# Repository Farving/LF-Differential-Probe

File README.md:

# Scope-Preamp-x1000
Differential input Scope preamp x1000 for measuring ground plane noise

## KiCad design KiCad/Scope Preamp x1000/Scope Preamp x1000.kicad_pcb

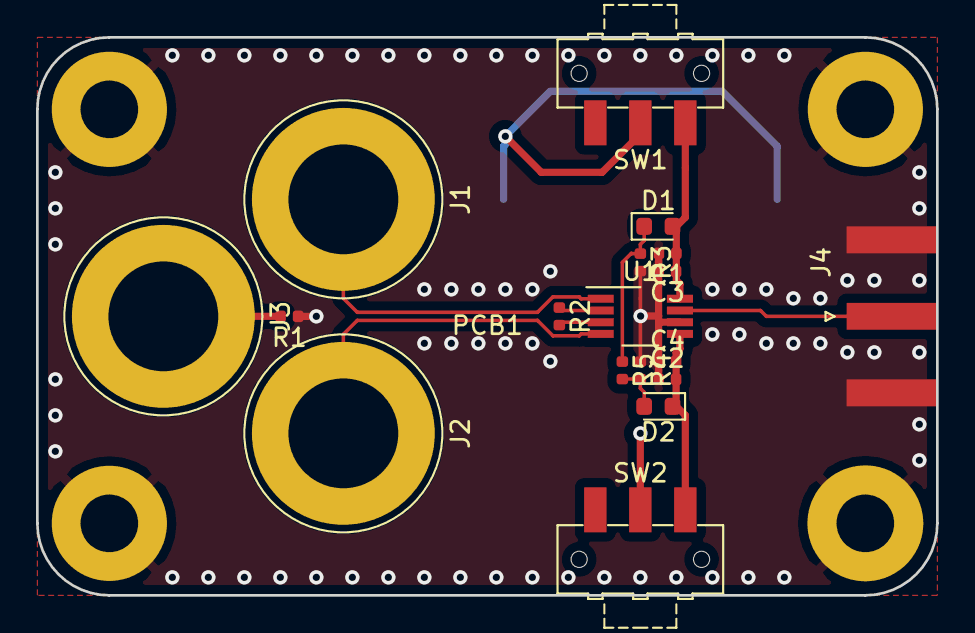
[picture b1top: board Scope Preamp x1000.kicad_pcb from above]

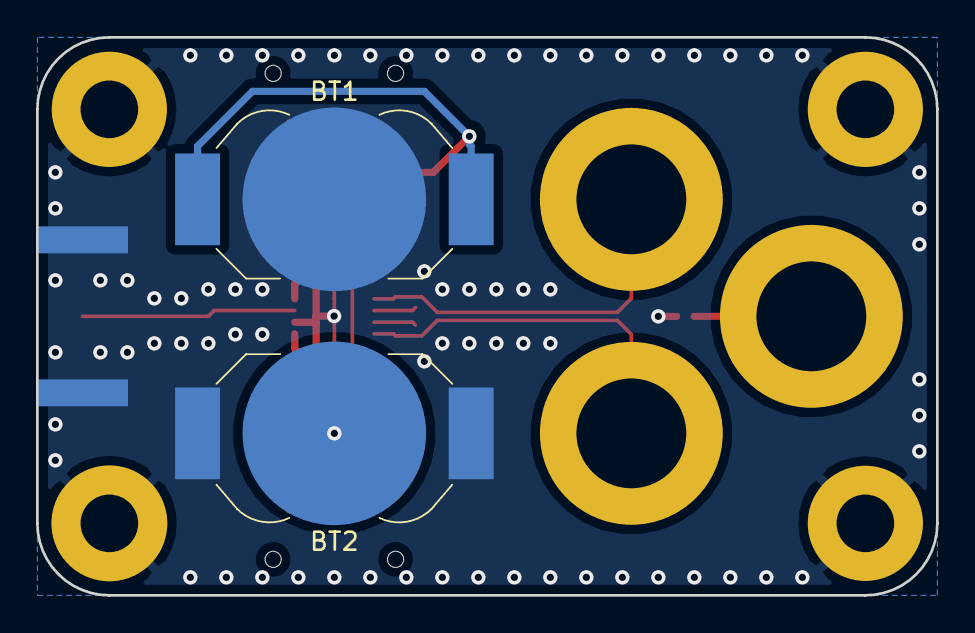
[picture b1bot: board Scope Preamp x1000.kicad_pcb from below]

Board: 2 copper layers, 50.0 x 31.0 mm, 21 parts (2 on the bottom side), 13 nets.

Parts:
BT1, BT2: CR2032; BatteryHolder_LINX_BAT-HLD-012-SMT
C1, C2: 10u; C_0402_1005Metric
C3, C4: 100n; C_0402_1005Metric
D1, D2: LED; LED_0603_1608Metric
J1, J2, J3: Conn_01x01_Male; Banana_Jack_1Pin
J4: Conn_Coaxial; SMA_Amphenol_132289_EdgeMount
PCB1: Board_Module; PCB_Board_50x31
R1: 10R; R_0402_1005Metric
R2, R3, R4, R5: 100R; R_0402_1005Metric
SW1, SW2: SW_SPDT; SW_SPDT_CK-JS102011SAQN
U1: INA826; VSSOP-8_3.0x3.0mm_P0.65mm

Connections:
/IN+: J2.1, U1.4
/IN-: J1.1, U1.1
GND: BT1.2, BT2.1, C1.2, C2.1, C3.2, C4.1, J4.2, PCB1.1, PCB1.2, PCB1.3, PCB1.4, R1.1, R3.2, R4.1, U1.6
unnamed: BT1.1, SW1.2
unnamed: BT2.2, SW2.2
unnamed: D1.1, R3.1, R5.1
unnamed: D2.2, R4.2, R5.2
unnamed: J3.1, R1.2
unnamed: J4.1, U1.7
unnamed: R2.1, U1.2
unnamed: R2.2, U1.3
VDD: C1.1, C3.1, D1.2, SW1.1, U1.8
VEE: C2.2, C4.2, D2.1, SW2.3, U1.5

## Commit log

2019-06-17 Add project
    Board module 50 x 31 mm
    Power on LED
    SMA output
    Banana input
    INA826 SSOP8
2019-06-17 Minor update
2019-06-20 Update gain resistor to achieve x1000
    Minor PCB update
